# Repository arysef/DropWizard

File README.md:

# DropWizard
Elex 327 Final Project: Device that measures how far it has been dropped.

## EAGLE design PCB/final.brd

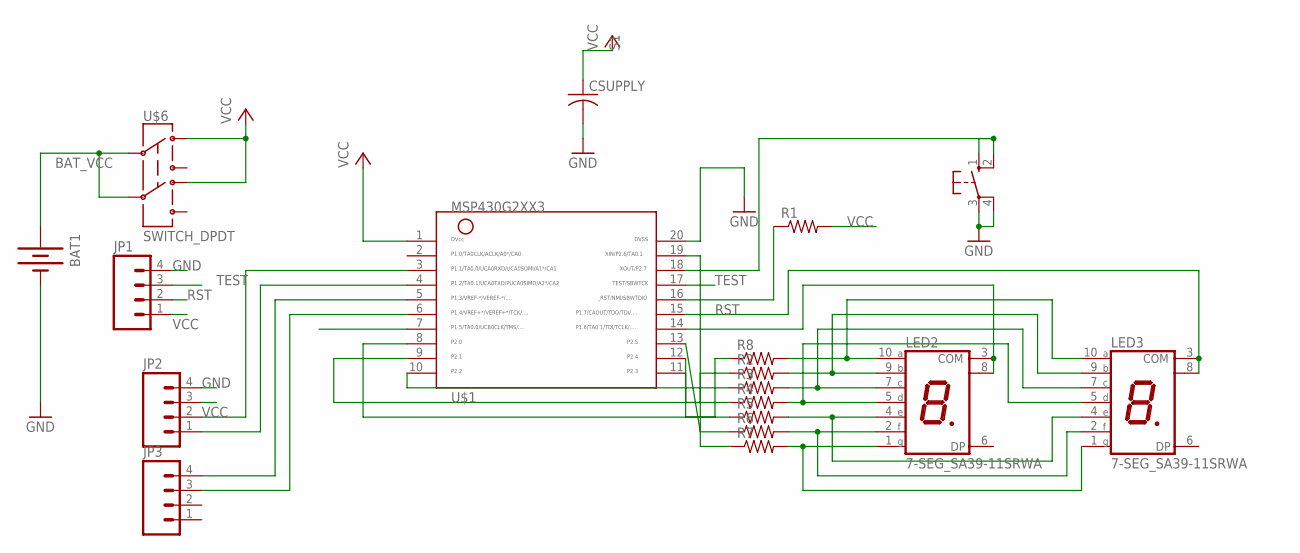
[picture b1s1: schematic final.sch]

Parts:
BAT1: BATTERYBU2032SM; BU2032SM
CSUPPLY: C-USC1206; C1206
JP1, JP2, JP3: M04LOCK; 1X04_LOCK
LED2, LED3: 7-SEG_SA39-11SRWA; SA39-11SRWA
R1, R2, R3, R4, R5, R6, R7, R8: R-US_R1206; R1206
S1: 10-XX; B3F-10XX
U$1: MSP430G2XX3TSSOP; PW20
U$6: SWITCH_DPDT; JS_DPDT_TH

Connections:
BAT_VCC: BAT1.P$1 (+), U$6.2, U$6.5
GND: BAT1.P$2 (-), CSUPPLY.2, JP1.4, JP2.4, S1.3, S1.4 (P1), U$1.20
unnamed: JP3.4, U$1.5
unnamed: R8.1, U$1.8
unnamed: R2.1, U$1.9
unnamed: R3.1, U$1.10
unnamed: R4.1, U$1.11
unnamed: R5.1, U$1.12
unnamed: R6.1, U$1.13
unnamed: R7.1, U$1.19
unnamed: LED2.3 (COM), LED2.8 (COM), U$1.14
unnamed: LED2.10 (A), LED3.10 (A), R8.2
unnamed: S1.1 (S), S1.2 (S1), U$1.18
unnamed: LED2.9 (B), LED3.9 (B), R2.2
unnamed: LED2.7 (C), LED3.7 (C), R3.2
unnamed: LED2.5 (D), LED3.5 (D), R4.2
unnamed: LED2.4 (E), LED3.4 (E), R5.2
unnamed: LED2.2 (F), LED3.2 (F), R6.2
unnamed: LED2.1 (G), LED3.1 (G), R7.2
unnamed: LED3.3 (COM), LED3.8 (COM), U$1.15
unnamed: JP2.2, U$1.3
unnamed: JP2.1, U$1.4
unnamed: JP3.3, U$1.6
RST: JP1.2, R1.1, U$1.16
TEST: JP1.3, U$1.17
VCC: CSUPPLY.1, JP1.1, JP2.3, R1.2, U$1.1, U$6.1, U$6.4

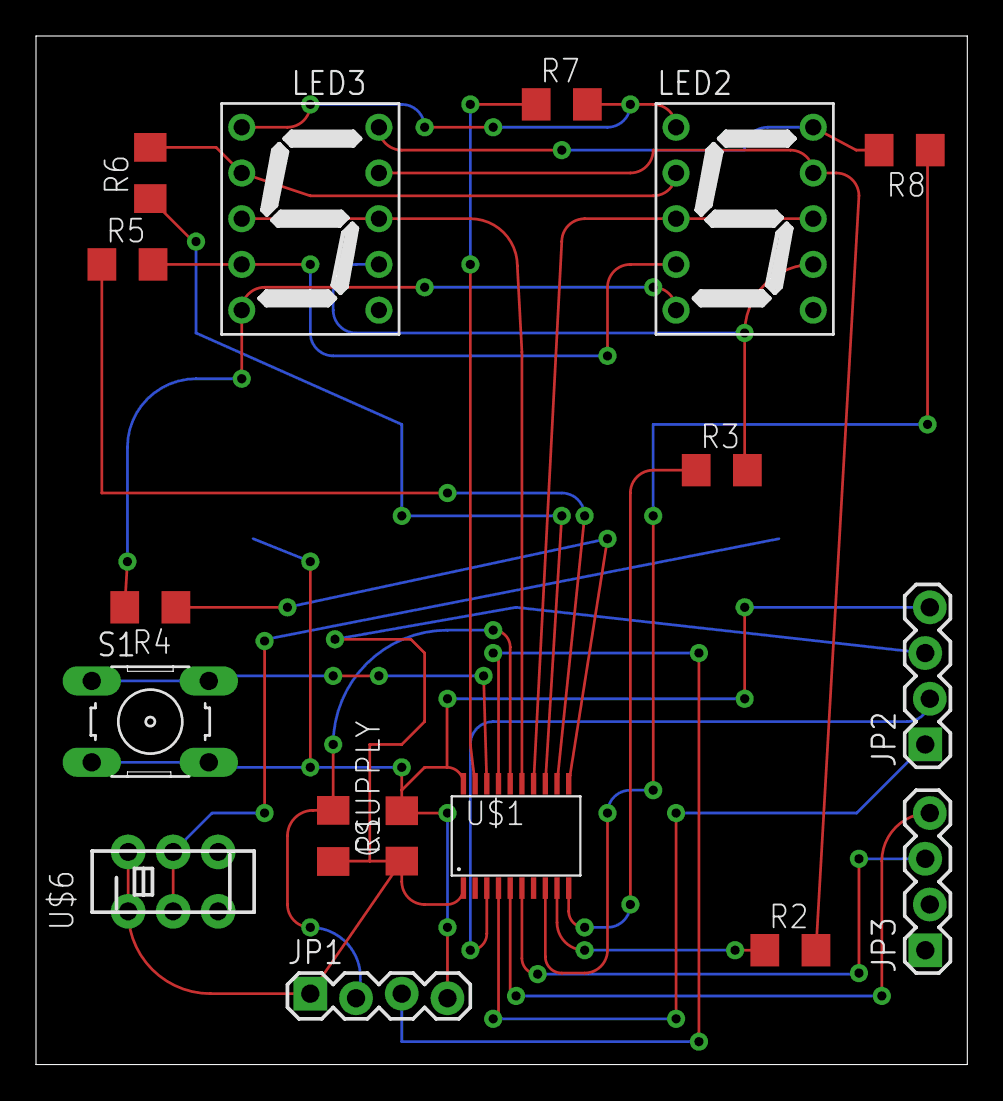
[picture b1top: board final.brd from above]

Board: 2 copper layers, 51.7 x 57.1 mm, 18 parts (1 on the bottom side), 26 nets.

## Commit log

2019-04-28 added initial code that can use seven seg display along with PCB board and schematic
2019-04-29 put together accelerometer and 7 seg display code
2019-04-29 can now use button to start point at which system is sensitive to shock: next step is to work on timer - current issue with timer is that trying to use watchdog timer, but doesn't seem to wake up fro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
2019-04-30 now works with provided PCB, can use 7 seg display and can count how long it was from button press to impact
2019-04-30 we now have a device that starts counting when a button is pressed and then stops when it is impacted
2019-04-30 finished initial project! this can be used to make a device that measures how far it is dropped
2019-04-30 added comments and changed magic numbers to constants

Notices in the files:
parts and their libraries:
SparkFun: Licensing: CC v3.0 Share-Alike You are welcome to use this library for commercial purposes.
